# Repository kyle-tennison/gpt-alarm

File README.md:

## Overview

Getting up in the morning sounds simple, but for many people, the hardest part is staying out of bed after the alarm goes off. Traditional alarms only solve half the problem: they can wake you up, but they can’t stop you from crawling back under the covers five minutes later.

Night Vision takes a different approach; it's an AI-powered alarm clock that uses an infrared camera and a fully local AI model to determine whether you’re still in bed. The alarm goes off at your set time, and only turns off when it sees you get out of bed. If the system detects that you’ve gone back to bed, the alarm starts again automatically. Once you’re actually up, it stays silent.

## Privacy

Having a camera pointed at your bed is unnerving to most people. However, it's really no different than having your phone camera near your bed. Nothing is being sent over the web: the photos are streamed directly to an on-prem vision-language model, and are never even written to disk. 

## Technical Overview

This project is implemented in Rust on a Jetson Orin Nano dev board. This is more of an embedded project than an AI project. Fast iteration is desired, so the following system was chosen in an attempt to maximize efficiency.

### GStreamer

The [`gstreamer-rs`](https://crates.io/crates/gstreamer) crate was used to implement GStreamer directly in Rust. This allows frames to be read directly from a callback function. This bypasses any network or file I/O, and doesn't need to make any kernel calls whatsoever because everything happens in shared memory[^1]. 

There is a bit of time lost between requesting a frame in the "Frame Request Mutex" and the time the callback is triggered. However, the current implementation prefers a more recent frame over the fastest frame. There is no point in running the loop on an old frame.

### Vision Language Model

[`llama.cpp`](https://github.com/ggml-org/llama.cpp) is used for all AI-related processing. It was recompiled to take full advantage of the NVIDIA hardware. The model of choice is a tiny 450M vision-language model from LiquidAI: [`LiquidAI/LFM2.5-VL-450M-GGUF`](https://huggingface.co/LiquidAI/LFM2.5-VL-450M-GGUF). With the NVIDIA chip, the entire loop, from image to prediction, takes 0.3s. 

### CAD Model

A public Onshape CAD model is provided [here](https://cad.onshape.com/documents/bcaebb5bd275e77d30be5dbb/w/f60a4044710e4fea0219c5aa/e/11bcaacbcd1531fb40906f8f?renderMode=0&uiState=6a0fc5f17abba21c43632f43). I was going for an 80s beige vibe, which a lot of people hate, but I personally love.

### PCB

A very simple PCB sits under the Jetson Orin Nano dev board. KiCad files for this are in `board/`. There is a spot for a relay here that is unused, but might be useful in a future version. The main purpose of this board is to operate the buzzer and an indicator LED.

## Unrelated

### 15-year-old Attempt

For a very long time, I've wanted an alarm clock that could detect when I was in bed. When I was 15, I tried a very similar approach using a *very* sketchy force transducer made from my parents' bathroom scale. This is what it looked like:

This worked for a couple of days, but I had to plug my laptop into it every night, so it didn't last long. I remember at the time contemplating running a CNN on a Raspberry Pi that could monitor a video feed of my bed. I actually found the blog post where I was thinking about this:

> "I also considered the option of training an AI to use a picture to determine if I was in bed or not. I also ended up deciding against this because of the sheer complexity."

From a [blog post](https://rannsyt.blogspot.com/2020/10/i-built-smart-bed-blog.html) in 2020.

And it's good that I dropped that idea, because a conventional CNN would be extremely sensitive to any change in the environment. That is if I could even get it trained in the first place. It would require a lot of training data, and the moment my room changed (new picture, different bedding, etc.), the model could easily start spitting out garbage.

[^1]: Don't quote me on the kernel part—I might be mistaken.

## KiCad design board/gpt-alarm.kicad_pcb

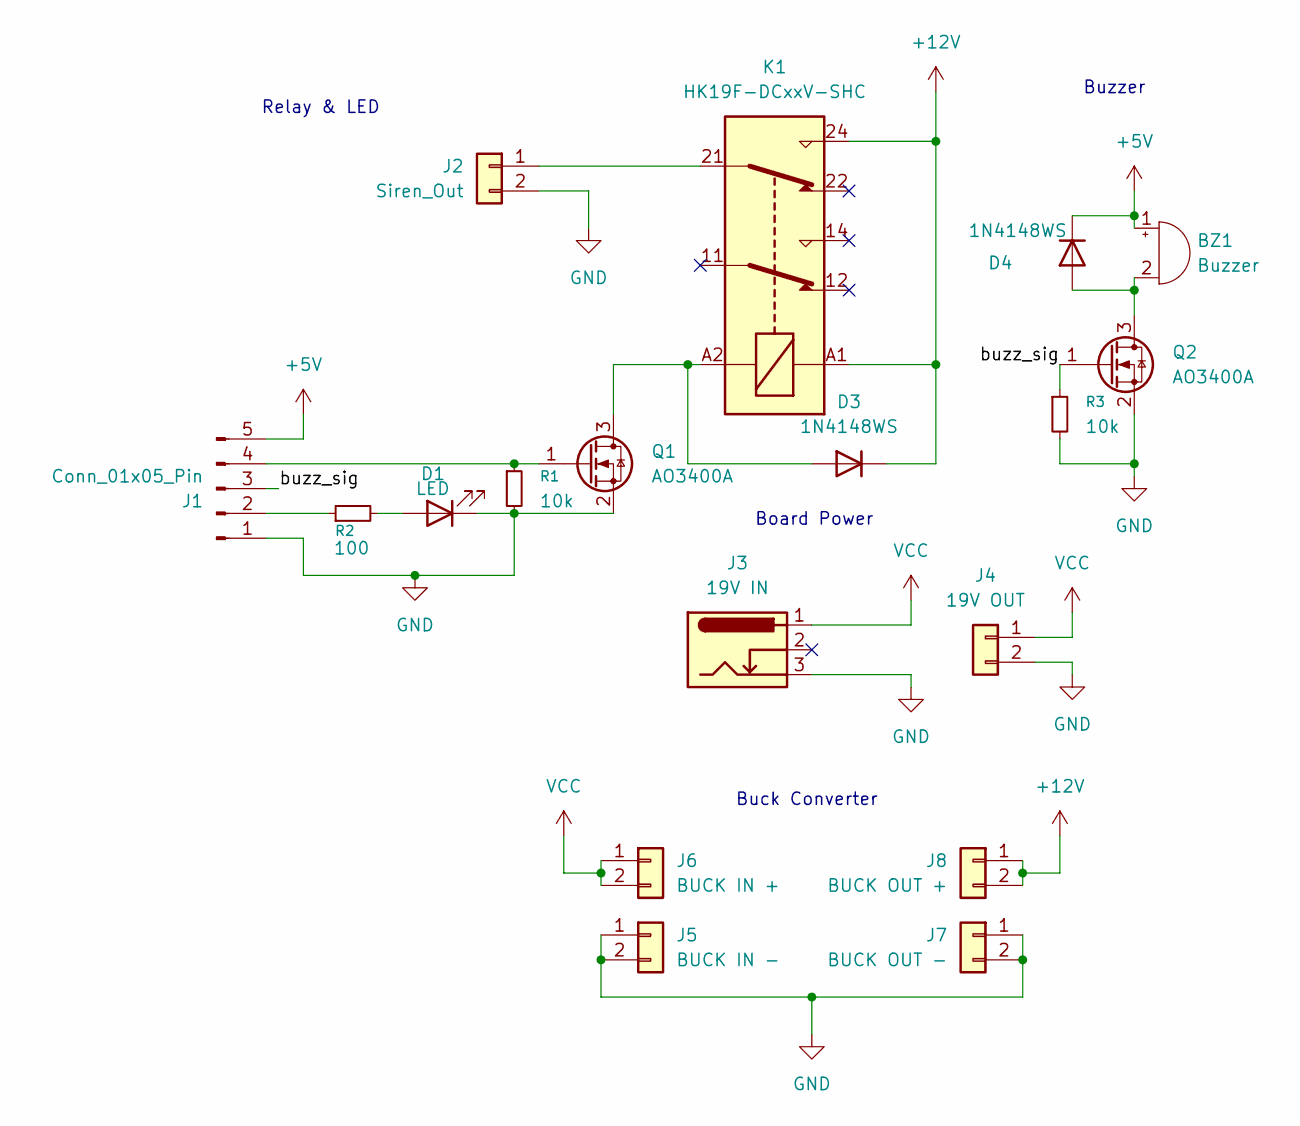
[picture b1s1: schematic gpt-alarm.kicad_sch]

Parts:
BZ1: Buzzer; MagneticBuzzer_StarMicronics_TMB
D1: LED; D_1206_3216Metric
D3, D4: 1N4148WS; D_SOD-323
J1: Conn_01x05_Pin; PinHeader_1x05_P2.54mm_Horizontal
J2: Siren_Out; TerminalBlock_Xinya_XY308-2.54-2P_1x02_P2.54mm_Horizontal
J3: 19V IN; BarrelJack_Horizontal
J4: 19V OUT; TerminalBlock_Xinya_XY308-2.54-2P_1x02_P2.54mm_Horizontal
J5: BUCK IN -; PinHeader_1x02_P2.54mm_Vertical
J6: BUCK IN +; PinHeader_1x02_P2.54mm_Vertical
J7: BUCK OUT -; PinHeader_1x02_P2.54mm_Vertical
J8: BUCK OUT +; PinHeader_1x02_P2.54mm_Vertical
K1: HK19F-DCxxV-SHC; Relay_DPDT_Finder_30.22
Q1, Q2: AO3400A; SOT-23
R1, R3: 10k; R_1206_3216Metric
R2: 100; R_1206_3216Metric

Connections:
+5V: BZ1.1 (+), D4.1 (K), J1.5
+12V: D3.1 (K), J8.1, J8.2, K1.24, K1.A1
/buzz_sig: J1.3, Q2.1 (G), R3.1
GND: D1.1 (K), J1.1, J2.2, J3.3, J4.2, J5.1, J5.2, J7.1, J7.2, Q1.2 (S), Q2.2 (S), R1.2, R3.2
unnamed: BZ1.2 (-), D4.2 (A), Q2.3 (D)
unnamed: D1.2 (A), R2.2
unnamed: D3.2 (A), K1.A2, Q1.3 (D)
unnamed: J1.2, R2.1
unnamed: J1.4, Q1.1 (G), R1.1
unnamed: J2.1, K1.21
VCC: J3.1, J4.1, J6.1, J6.2

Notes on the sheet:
Relay & LED
Buck Converter
Board Power
Buzzer

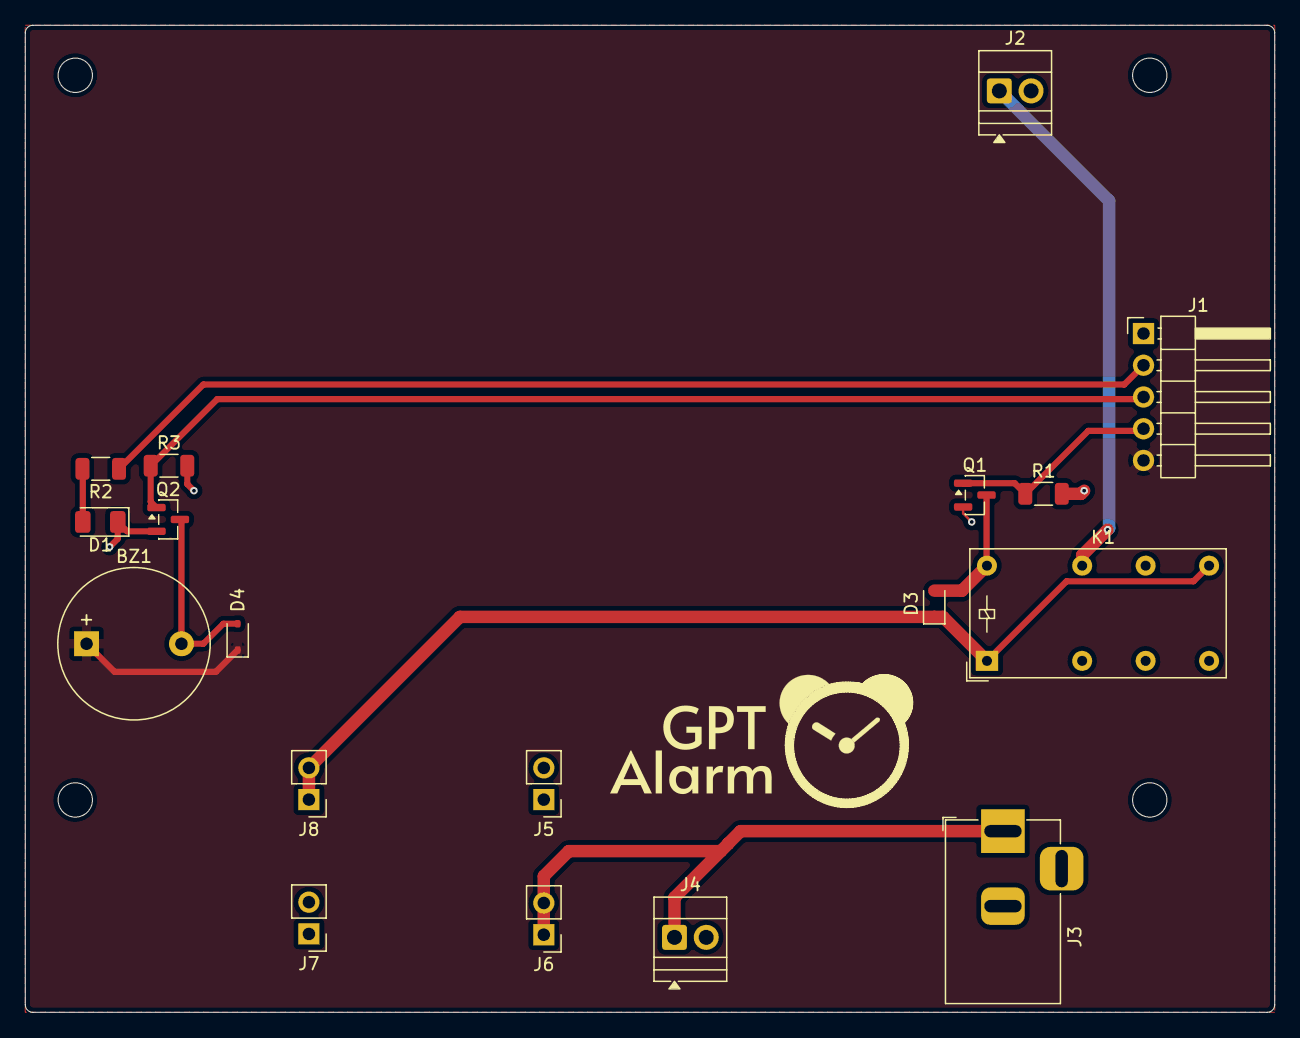
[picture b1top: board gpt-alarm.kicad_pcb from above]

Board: 2 copper layers, 100.0 x 79.0 mm, 18 parts (0 on the bottom side), 11 nets.

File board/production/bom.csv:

Designator,Footprint,Quantity,Value,LCSC Part #
BZ1,MagneticBuzzer_StarMicronics_TMB,1,Buzzer,
D1,1206,1,LED,
"D3, D4",D_SOD-323,2,1N4148WS,
J1,PinHeader_1x05_P2.54mm_Horizontal,1,Conn_01x05_Pin,
J2,TerminalBlock_Xinya_XY308-2.54-2P_1x02_P2.54mm_Horizontal,1,Siren_Out,
J3,BarrelJack_Horizontal,1,19V IN,
J4,TerminalBlock_Xinya_XY308-2.54-2P_1x02_P2.54mm_Horizontal,1,19V OUT,
J5,PinHeader_1x02_P2.54mm_Vertical,1,BUCK IN -,
J6,PinHeader_1x02_P2.54mm_Vertical,1,BUCK IN +,
J7,PinHeader_1x02_P2.54mm_Vertical,1,BUCK OUT -,
J8,PinHeader_1x02_P2.54mm_Vertical,1,BUCK OUT +,
K1,Relay_DPDT_Finder_30.22,1,HK19F-DCxxV-SHC,
"Q1, Q2",SOT-23,2,AO3400A,
"R1, R3",1206,2,10k,
R2,1206,1,100,

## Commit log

2026-04-11 feat: first working pipeline
2026-04-12 perf: smaller model
2026-04-12 perf: threaded camera
2026-04-12 perf: resize camera at startup
2026-04-12 feat: sound on positive with running avg
2026-04-12 feat: better alarm
2026-04-12 chore: update readme and lock
2026-04-12 lint
2026-04-12 perf: queue images
2026-04-12 feat: carrier schematic
2026-04-13 feat: pcb layout
2026-04-13 doc: update README.md
2026-04-13 doc: update readme for investors
2026-04-13 doc: really lay it in
2026-05-16 feat: gst camera
2026-05-17 feat: buzzer impl
2026-05-17 feat: startup tests
2026-05-17 feat: integrate pipeline
2026-05-18 fix: use appsink for image pipeline
2026-05-18 wip: led service
2026-05-20 fix: memory runaway
2026-05-20 feat/nv rewrite (#1)
    * feat: gst camera
    * feat: buzzer impl
    * feat: startup tests
    * feat: integrate pipeline
    * lint
    * fix: use appsink for image pipeline
2026-05-20 chore: clippy
2026-05-20 feat: dispatcher
2026-05-22 doc: update readme
2026-05-22 doc: update banner
2026-05-22 feat/hibernation (#2)
    * chore: clippy
    * feat: dispatcher
    * doc: update readme
    * doc: update banner
    * doc: update readme
2026-05-22 chore: rename bin
2026-05-22 fix: loop when update
2026-05-22 fix: missed renames
2026-05-22 fix: misc bugs
2026-05-22 doc: fix readme
2026-05-22 feat: kill script
2026-05-22 chore: remove dead files
2026-05-26 feat: kill llama in kill script
2026-05-26 feat: always active flag
2026-05-26 feat: systemd unit for process
